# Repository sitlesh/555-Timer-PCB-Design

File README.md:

# 555 Timer Based Astable Multivibrator PCB Design

A manufacturing-ready, optimized 2-layer PCB layout for a 555 Timer Astable Multivibrator circuit, designed using **KiCad 10.0**. This project demonstrates industry-standard PCB design practices, including schematic capture, component placement optimization, ground plane design, and DRC compliance.

---

## 🚀 Key Technical Specifications & Features
* **Component Placement:** Optimized for minimal trace lengths and efficient routing paths.
* **Layer Count:** 2-Layer PCB (Top and Bottom Copper).
* **Power & Grounding:** Integrated a dedicated **Ground Plane (GND Pour)** on the copper layers to ensure signal integrity and minimize electromagnetic interference (EMI).
* **Design Rule Check (DRC):** 100% compliant with industry manufacturing constraints (**0 Errors / 0 Warnings**).
* **Fabrication Ready:** Standard **Gerber (X2)** and **Excellon Drill files** generated for seamless manufacturing.

---

## 🛠️ Visuals & Design Layout

### 1. 3D Render View

### 2. PCB Layout
#### Top Layer Layout

#### Bottom Layer Layout

---

## 💡 Engineering Challenges & Key Learnings
* **Ground Net Alignment:** Initially encountered DRC errors regarding unconnected ground pins. Solved by correctly binding the copper zone boundaries to the `GND` net, allowing automated copper flow across all ground pads.
* **Isolated Copper Islands:** Fixed potential manufacturing issues with isolated copper pours by tuning the zone properties and enabling automated island removal, maintaining a clean and effective ground return path.
* **Thermal Relief vs Solid Connections:** Analyzed pad connection types to balance between robust electrical connectivity and ease of manual soldering.

---

## 📁 File Structure

* **[`led flasher.kicad_sch`](./led%20flasher.kicad_sch)** - Schematic capture file.
* **[`led flasher.kicad_pcb`](./led%20flasher.kicad_pcb)** - PCB Layout file.
* **[`Gerbers.zip`](./Gerbers.zip)** - Production-ready Gerber and Drill files for manufacturing (compatible with JLCPCB, PCBWay, etc.).
---
*Designed with 💻 using KiCad.*

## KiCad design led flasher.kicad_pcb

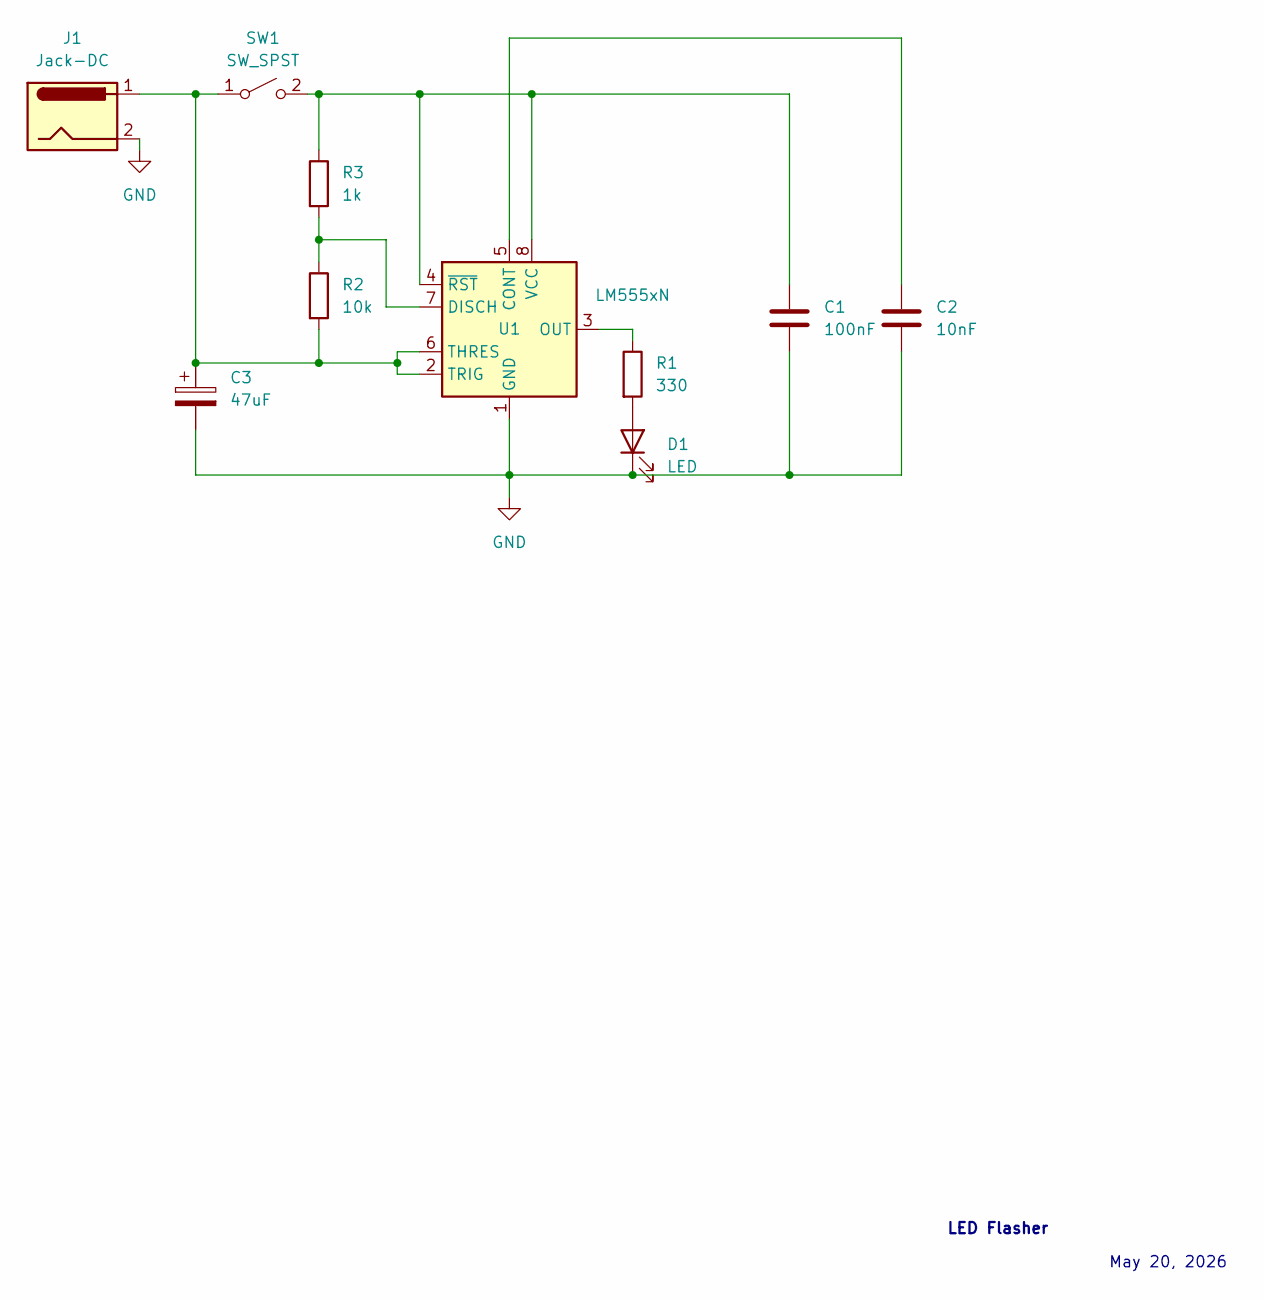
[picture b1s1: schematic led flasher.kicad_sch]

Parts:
C1: 100nF; C_Disc_D5.0mm_W2.5mm_P5.00mm
C2: 10nF; C_Disc_D5.0mm_W2.5mm_P5.00mm
C3: 47uF; CP_Radial_D5.0mm_P2.00mm
D1: LED; LED_D5.0mm
J1: Jack-DC; TerminalBlock_MaiXu_MX126-5.0-02P_1x02_P5.00mm
R1: 330; R_Axial_DIN0207_L6.3mm_D2.5mm_P7.62mm_Horizontal
R2: 10k; R_Axial_DIN0207_L6.3mm_D2.5mm_P7.62mm_Horizontal
R3: 1k; R_Axial_DIN0207_L6.3mm_D2.5mm_P7.62mm_Horizontal
SW1: SW_SPST; SW_PUSH-12mm
U1: LM555xN; DIP-8_W7.62mm

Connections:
GND: C1.2, C2.2, C3.2, D1.1 (K), J1.2, U1.1 (GND)
unnamed: D1.2 (A), R1.2
unnamed: C3.1, J1.1, R2.2, SW1.1 (A), U1.2 (TRIG), U1.6 (THRES)
unnamed: C1.1, R3.1, SW1.2 (B), U1.4 (~RST), U1.8 (VCC)
unnamed: C2.1, U1.5 (CONT)
unnamed: R2.1, R3.2, U1.7 (DISCH)
unnamed: R1.1, U1.3 (OUT)

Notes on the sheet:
LED Flasher
May 20, 2026

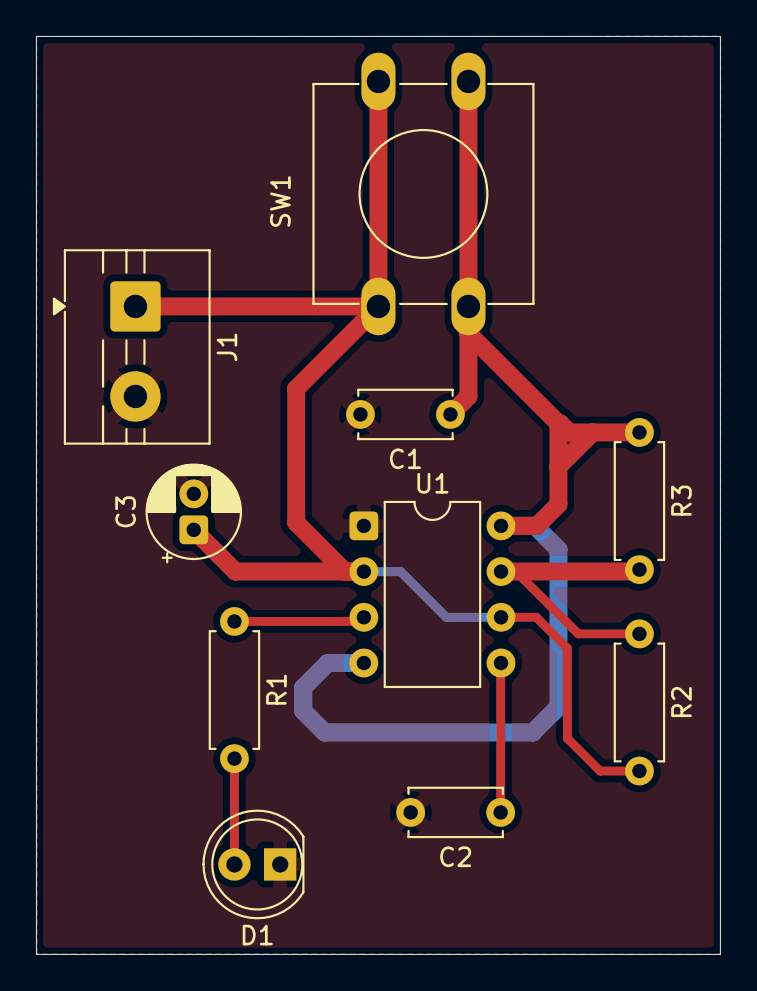
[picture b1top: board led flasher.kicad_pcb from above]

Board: 2 copper layers, 38.0 x 51.0 mm, 10 parts (0 on the bottom side), 7 nets.

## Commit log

2026-05-20 Create led flasher schematic
2026-05-20 Rename Garbers.zip to Gerbers.zip
